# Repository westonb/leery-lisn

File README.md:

# leery-lisn
### A open source dual AC LISN with integrated common mode / differential mode separator and transient limiter.

**Schematic [here](doc/lisn-pcb.pdf)**

## Summary
The leery-lisn is a Line Impedance Stabilization Network (LISN) for pre-compliance conducted EMI measurements of devices that plug into the AC line.
A LISN goes between a device and the AC outlet and provides a known AC line impedance, allowing for repeatable measurements of conducted noise generated by the device.
It also contains circuitry to couple the noise to a 50 ohm RF output to allow for measurement with a spectrum analyzer.

The leery-lisn contains a LISN network on both the neutral and line connections of the AC plug and a common mode / differential mode separator, allowing for measurement of both the differential mode and common mode noise generated by a device.
It also contains a transient limiter to protect a connected spectrum analyzer from transients on the AC line or plugging the LISN into the AC line when the spectrum analyzer is already connected.

The design of the leery-lisn is loosely based on the LISN designs from this [thread](https://www.eevblog.com/forum/projects/5uh-lisn-for-spectrum-analyzer-emcemi-work/) on the EEVBlog forum, as well as the designs for a [common mode / differential mode separator](https://www.eevblog.com/forum/projects/diy-dm-cm-seperator-for-emc-lisn-mate/) and this [transient limiter](https://www.eevblog.com/forum/projects/transient-limiter-for-spectrum-analyzer-protection/).

## Specifications & Operation
The leery-lisn is a 50uH LISN, which is the typical impedance value for conducted emissions testing between 150KHz - 30MHz, as specified in standards such as CISPR16.
The leery-lisn is designed for a maximum input / output voltage of 240V, although the output plug is fixed as a US style 120V plug.
The current rating is 5A RMS.

Due to the transient limiter, the common mode and differential mode outputs have 10dB of attenuation.
For proper separation of the common mode and differential mode signals the unused output should be attenuated into 50 ohms.

The leery-lisn contains 8.1uF of capacitance between each AC leg and ground to decouple the LISN impedance from the impedance of the AC line.
Due to the high ground currents resulting from this capacitance, consider using a isolation transformer between the AC line and the leery-lisn.

## Performance
S21 measurements were taken of the leery-lisn to verify correct operation of the common mode / differential mode separator and impedance measurements were taken to check compliance with CISPR16 standard.

A very cursed adaptor was created to connect the AC output of the LISN to a VNA and measurements were taken with the AC input to the VNA shorted.

The leery-lisn is a three port device, so it can not be fully characterized with a two port VNA.
However, a resistive splitter allows for accurately measuring the common mode S21 and the common mode rejection.

If it is assumed that driving one input to the LISN with the other terminated into 50 ohms provides a even split of common mode and differential mode stimulus, the differential mode S21 can also be measured.

The impedance of the two legs can also be compared against the CISPR16 standard, which provides a table of frequency vs the allowable |Z| and phase of the LISN input impedance.
From the plot below it can be seen that the line leg of the LISN is slightly out of spec above 25MHz due to an extra 2" of wire running between the AC connector and the PCB.
This is also the cause of the difference in the differential mode response for the two inputs of the LISN.
leery-lisn technically does not meet the CISPR16 requirements, but should be close enough for pre-compliance work.

## Construction
The leery-lisn is completely open source and the PCB design for the LISN and the front and back panels are provided in this repository.

Parts not on the BOM for the PCB are:

| Description  | Quantity | Part Number     |
|--------------|----------|-----------------|
| Enclosure    | 1        | 1455T1601BU     |
| Fuse Holder  | 2        | 696211001102    |
| AC Outlet    | 1        | 3-119-052       |
| Power Switch | 1        | H8550VBBBEN551W |
| AC Inlet     | 1        | 1-6609987-4     |

## Improvements
A bleeder resistor should be added across the input capacitors to discharge them.

The impedance of the line side of the LISN is slightly outside of the limits specified in the CISPR16 standards due to the added wire length between the AC plug on the left side of the panel and the line input on the PCB, which is on the right.
The front panel could be redone to reduce this wire length.

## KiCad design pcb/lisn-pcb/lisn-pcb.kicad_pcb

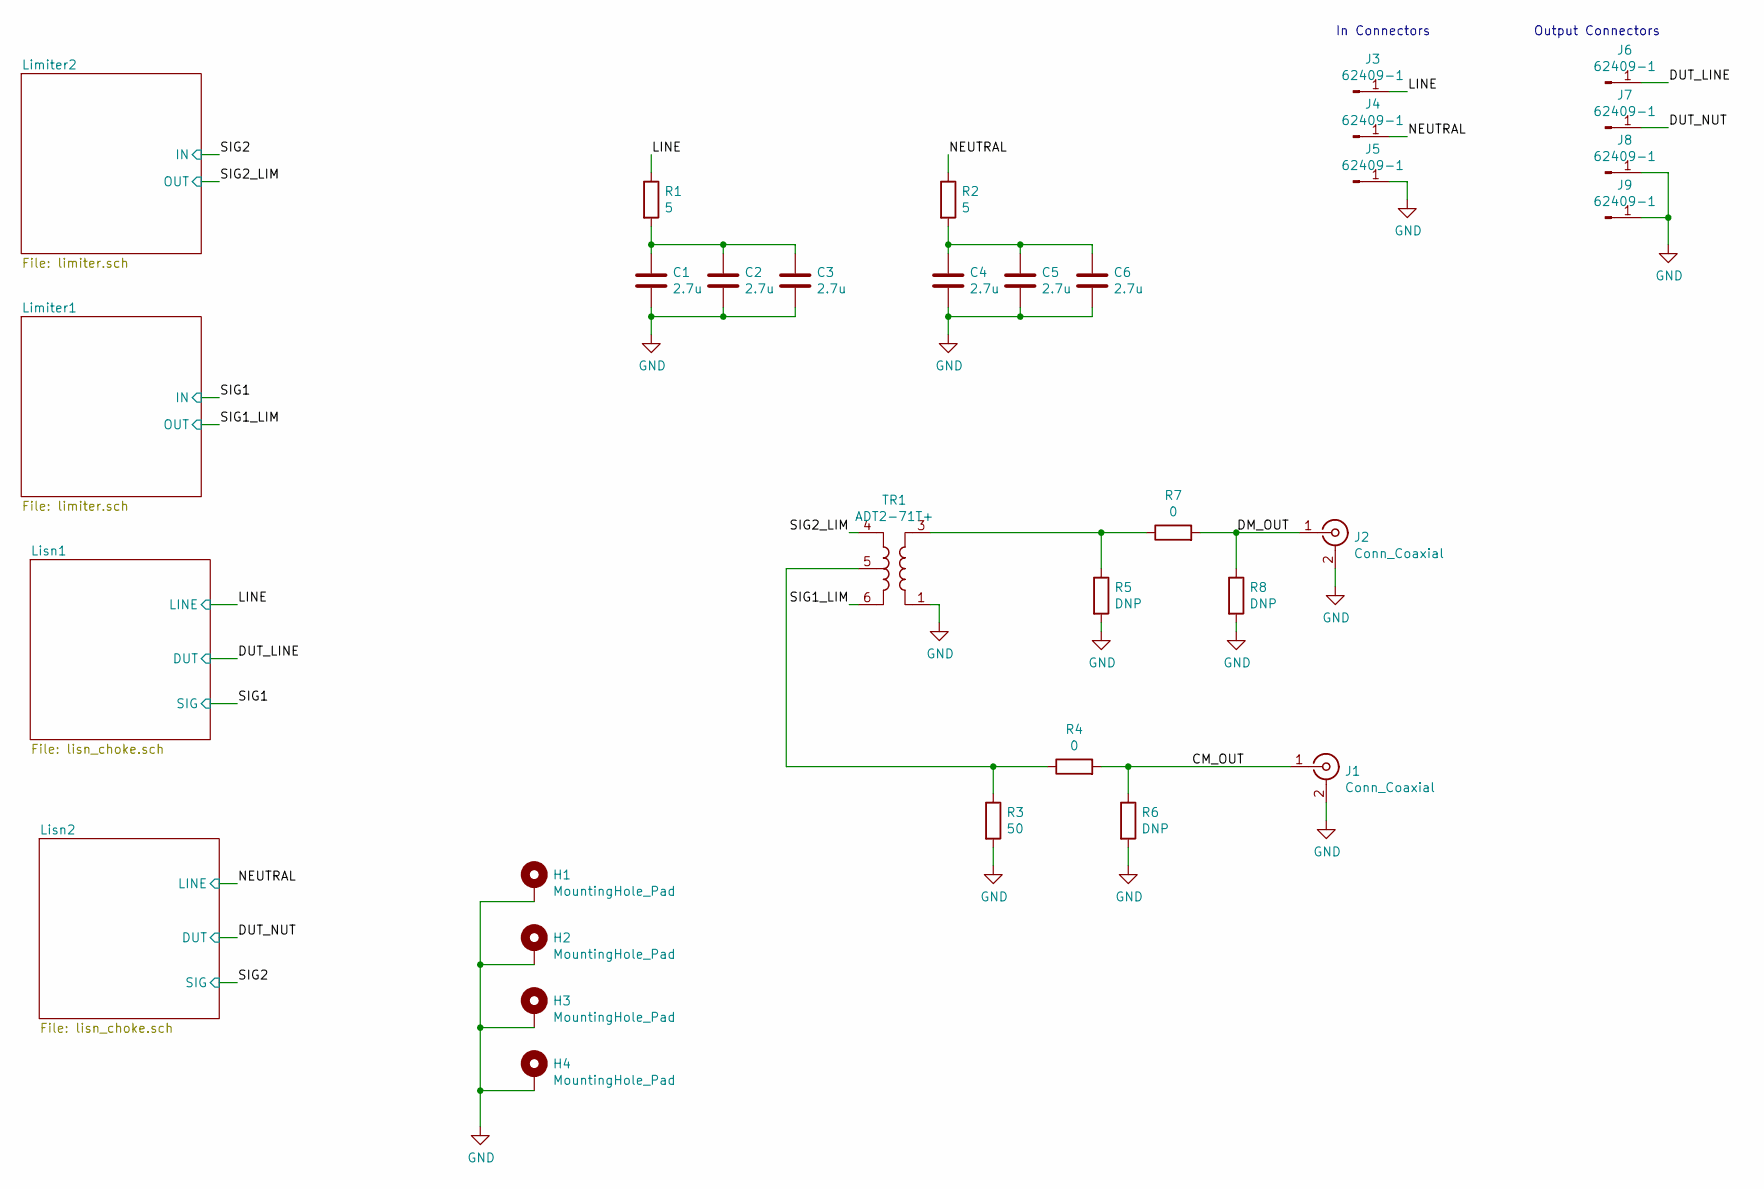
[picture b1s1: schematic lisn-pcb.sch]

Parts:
C1, C2, C3, C4, C5, C6: 2.7u; C_Rect_L31.5mm_W20.0mm_P27.50mm_MKS4; MPN ECQ-UAAF275K
H1, H2, H3, H4: MountingHole_Pad; M3-tight-fit-socket-head
J1, J2: Conn_Coaxial; SMA_Amphenol_132203-12_Horizontal; MPN 619540-1
J3, J4, J5, J6, J7, J8, J9: 62409-1; MPN 62409-1
R1, R2: 5; R_Axial_Power_L20.0mm_W6.4mm_P25.40mm; MPN WNE5R0FET
R3: 50; R_0805_2012Metric; MPN RNCP0805FTD49R9
R4, R7: 0; R_0805_2012Metric; MPN RC0805JR-070RL
R5, R6, R8: DNP; R_0805_2012Metric
TR1: ADT2-71T+; Mini-Circuits_CD637_H5.23mm; MPN ADT2-71T+

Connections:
/CM_OUT: J1.1 (In), R4.2, R6.1
/DM_OUT: J2.1 (In), R7.2, R8.1
/DUT_LINE: J6.1; also elsewhere on the board
/DUT_NUT: J7.1; also elsewhere on the board
/LINE: J3.1, R1.1; also elsewhere on the board
/NEUTRAL: J4.1, R2.1; also elsewhere on the board
/SIG1_LIM: TR1.6; also elsewhere on the board
/SIG2_LIM: TR1.4; also elsewhere on the board
GND: C1.2, C2.2, C3.2, C4.2, C5.2, C6.2, H1.1, H2.1, H3.1, H4.1, J1.2 (Ext), J2.2 (Ext), J5.1, J8.1, J9.1, R3.2, R5.2, R6.2, R8.2, TR1.1; also elsewhere on the board
unnamed: C1.1, C2.1, C3.1, R1.2
unnamed: C4.1, C5.1, C6.1, R2.2
unnamed: R3.1, R4.1, TR1.5
unnamed: R5.1, R7.1, TR1.3

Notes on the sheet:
In Connectors
Output Connectors

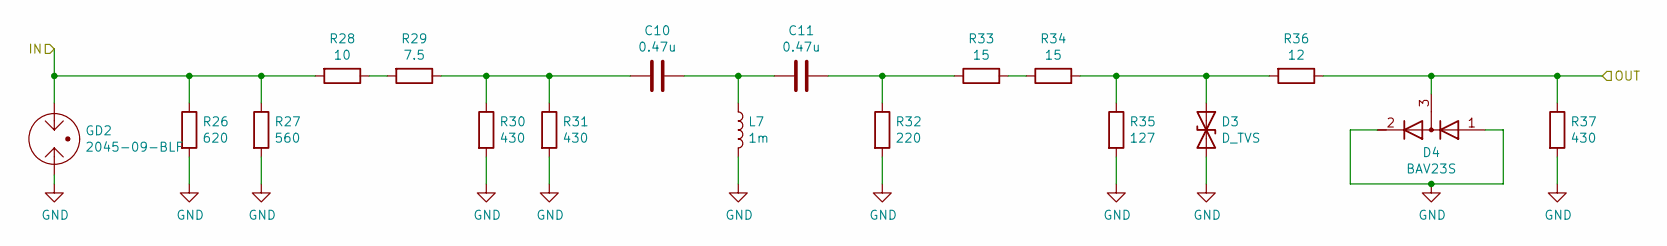
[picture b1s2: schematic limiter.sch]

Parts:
C7, C8: 0.47u; C_0805_2012Metric; MPN 08051C474K4Z2A
D1: D_TVS; D_SOD-323; MPN STS321050B100
D2: BAV23S; SOT-23; MPN BAV23S,215
GD1: 2045-09-BLF; GDT_Bourns_2045; MPN 2045-09-BLF
L1: 1m; L_BOURNS_PM1812; MPN PM1812-102J-RC
R9: 620; R_0805_2012Metric; MPN RCS0805620RFKEA
R10: 560; R_0805_2012Metric; MPN RCS0805560RFKEA
R11: 10; R_0805_2012Metric; MPN RCS080510R0FKEA
R12: 7.5; R_0805_2012Metric; MPN RCS08057R50FKEA
R13, R14, R20: 430; R_0805_2012Metric; MPN ESR10EZPF4300
R15: 220; R_0805_2012Metric; MPN RCS0805220RFKEA
R16, R17: 15; R_0805_2012Metric; MPN RCS080515R0FKEA
R18: 127; R_0805_2012Metric; MPN RK73H2ATTD1270F
R19: 12; R_0805_2012Metric; MPN ERJ-6ENF12R0V

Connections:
/SIG1: GD1.1, R9.1, R10.1, R11.2; also elsewhere on the board
/SIG1_LIM: D2.3 (common), R19.1, R20.1; also elsewhere on the board
GND: D1.2 (A2), D2.1 (A), D2.2 (K), GD1.2, L1.2, R9.2, R10.2, R13.2, R14.2, R15.2, R18.2, R20.2; also elsewhere on the board
unnamed: C7.1, C8.2, L1.1
unnamed: C7.2, R12.1, R13.1, R14.1
unnamed: C8.1, R15.1, R16.1
unnamed: D1.1 (A1), R17.2, R18.1, R19.2
unnamed: R11.1, R12.2
unnamed: R16.2, R17.1

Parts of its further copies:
C10, C11: 0.47u; C_0805_2012Metric; MPN 08051C474K4Z2A
D3: D_TVS; D_SOD-323; MPN STS321050B100
D4: BAV23S; SOT-23; MPN BAV23S,215
GD2: 2045-09-BLF; GDT_Bourns_2045; MPN 2045-09-BLF
L7: 1m; L_BOURNS_PM1812; MPN PM1812-102J-RC
R26: 620; R_0805_2012Metric; MPN RCS0805620RFKEA
R27: 560; R_0805_2012Metric; MPN RCS0805560RFKEA
R28: 10; R_0805_2012Metric; MPN RCS080510R0FKEA
R29: 7.5; R_0805_2012Metric; MPN RCS08057R50FKEA
R30, R31, R37: 430; R_0805_2012Metric; MPN ESR10EZPF4300
R32: 220; R_0805_2012Metric; MPN RCS0805220RFKEA
R33, R34: 15; R_0805_2012Metric; MPN RCS080515R0FKEA
R35: 127; R_0805_2012Metric; MPN RK73H2ATTD1270F
R36: 12; R_0805_2012Metric; MPN ERJ-6ENF12R0V

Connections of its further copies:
/SIG2: GD2.1, R26.1, R27.1, R28.2; also elsewhere on the board
/SIG2_LIM: D4.3 (common), R36.1, R37.1; also elsewhere on the board
GND: D3.2 (A2), D4.1 (A), D4.2 (K), GD2.2, L7.2, R26.2, R27.2, R30.2, R31.2, R32.2, R35.2, R37.2; also elsewhere on the board
unnamed: C10.1, C11.2, L7.1
unnamed: C10.2, R29.1, R30.1, R31.1
unnamed: C11.1, R32.1, R33.1
unnamed: D3.1 (A1), R34.2, R35.1, R36.2
unnamed: R28.1, R29.2
unnamed: R33.2, R34.1

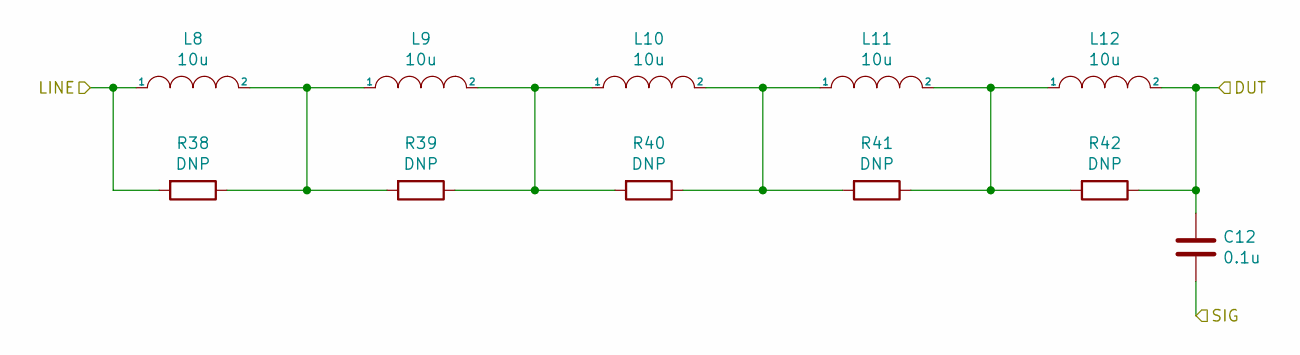
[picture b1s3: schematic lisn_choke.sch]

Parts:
C9: 0.1u; C_Rect_L26.5mm_W10.5mm_P22.50mm_MKS4; MPN BFC233860104
L2, L3, L4, L5, L6: 10u; L_WURTH_WE-HCC-1090; MPN 7443331000
R21, R22, R23, R24, R25: DNP; R_1206_3216Metric

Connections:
/DUT_LINE: C9.1, L6.2, R25.1; also elsewhere on the board
/LINE: L2.1, R21.2; also elsewhere on the board
/SIG1: C9.2; also elsewhere on the board
unnamed: L2.2, L3.1, R21.1, R22.2
unnamed: L3.2, L4.1, R22.1, R23.2
unnamed: L4.2, L5.1, R23.1, R24.2
unnamed: L5.2, L6.1, R24.1, R25.2

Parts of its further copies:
C12: 0.1u; C_Rect_L26.5mm_W10.5mm_P22.50mm_MKS4; MPN BFC233860104
L8, L9, L10, L11, L12: 10u; L_WURTH_WE-HCC-1090; MPN 7443331000
R38, R39, R40, R41, R42: DNP; R_1206_3216Metric

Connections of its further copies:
/DUT_NUT: C12.1, L12.2, R42.1; also elsewhere on the board
/NEUTRAL: L8.1, R38.2; also elsewhere on the board
/SIG2: C12.2; also elsewhere on the board
unnamed: L8.2, L9.1, R38.1, R39.2
unnamed: L9.2, L10.1, R39.1, R40.2
unnamed: L10.2, L11.1, R40.1, R41.2
unnamed: L11.2, L12.1, R41.1, R42.2

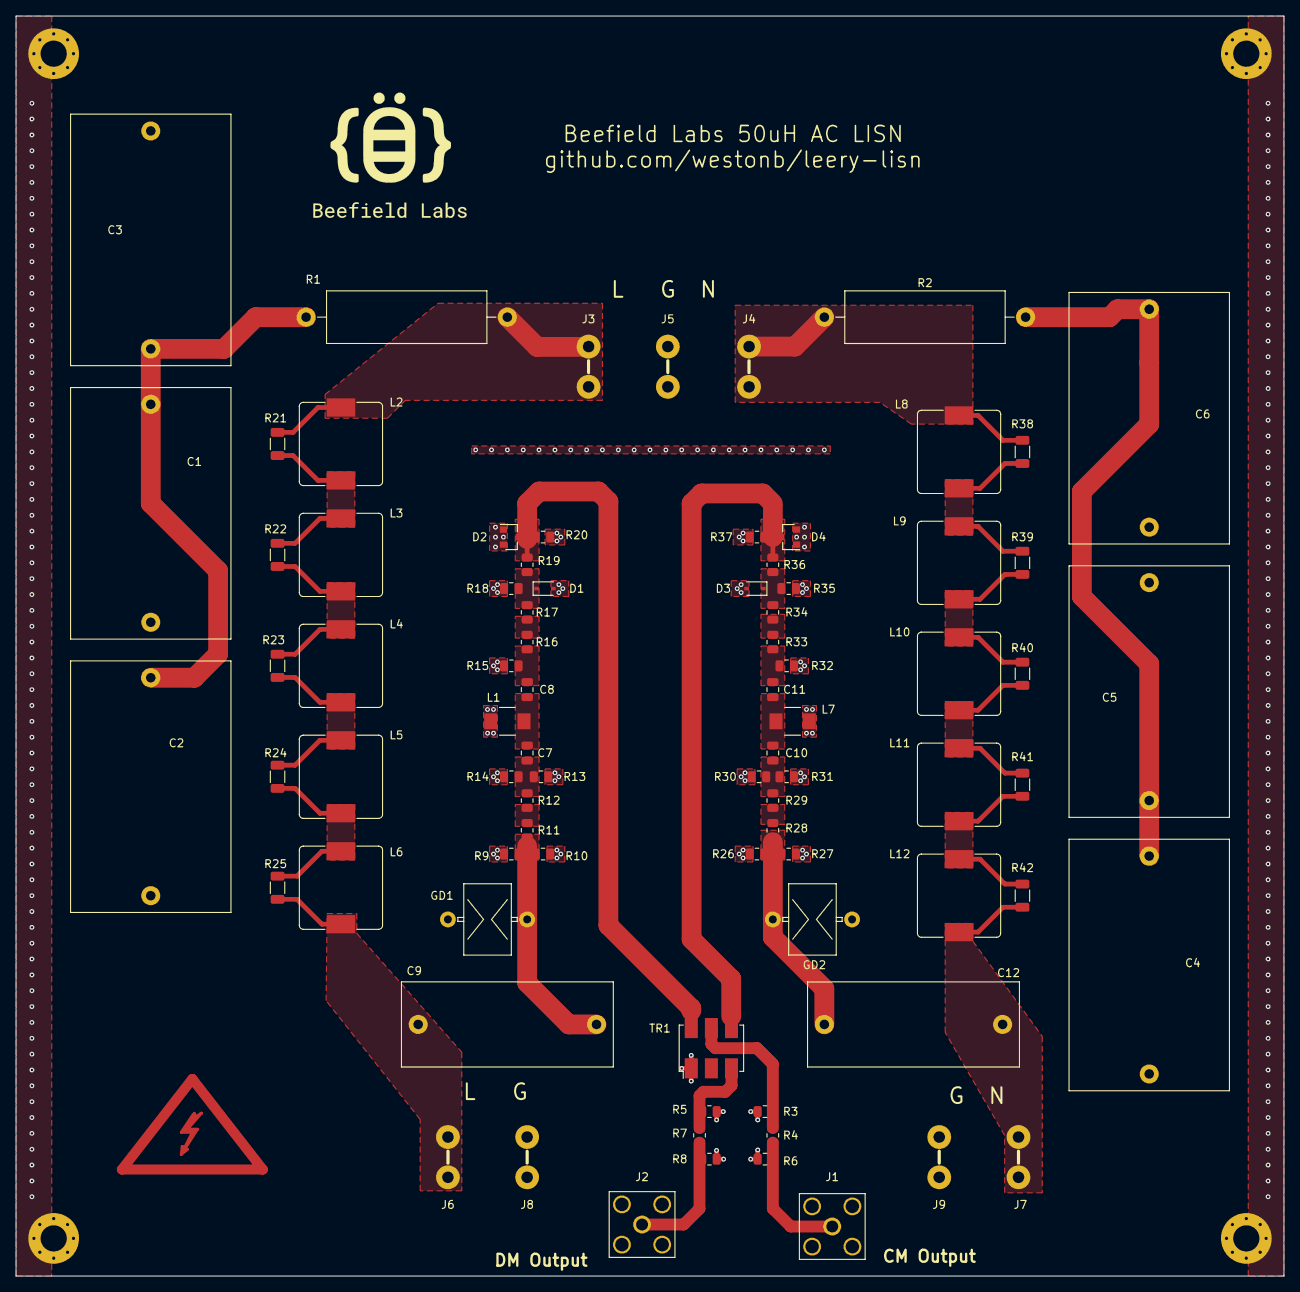
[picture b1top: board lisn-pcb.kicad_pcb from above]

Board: 2 copper layers, 160.0 x 159.0 mm, 86 parts (0 on the bottom side), 35 nets.

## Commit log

2021-08-09 inital schematic and sims
2021-08-13 added mcad
2021-08-15 finished PCB routing
2021-08-15 generated front and back panel dxf outlines
2021-08-21 V1 pcb design finished
2021-09-28 added LISN impedance and S21 measurements
2021-09-28 updated plots and readme
